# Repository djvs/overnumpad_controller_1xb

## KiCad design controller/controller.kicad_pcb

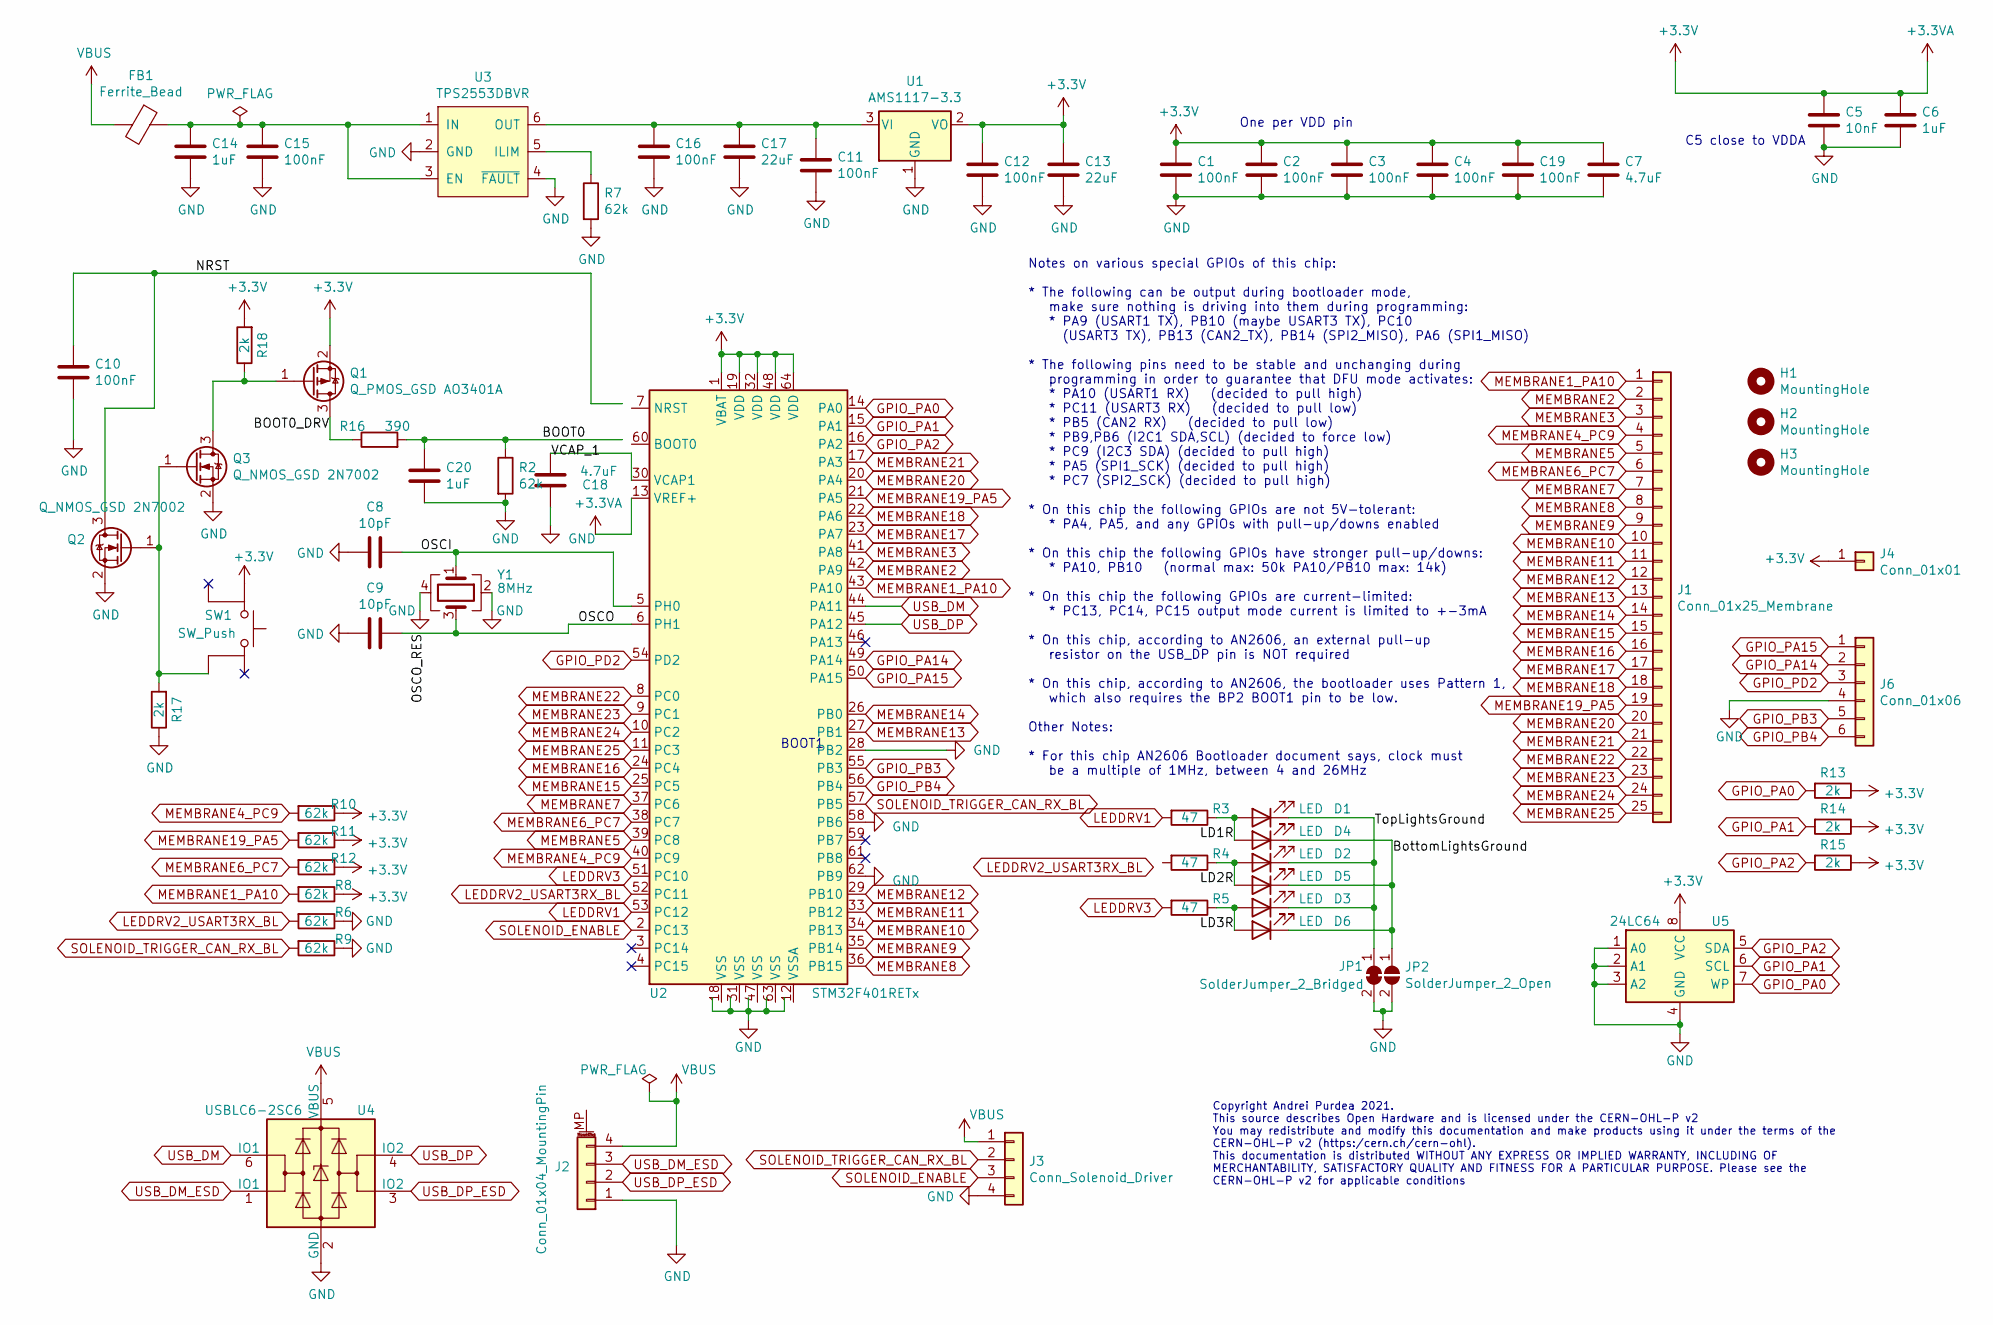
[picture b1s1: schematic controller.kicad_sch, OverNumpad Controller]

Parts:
C1, C2, C3, C4, C10, C11, C12, C15, C16, C19: 100nF; C_0805_2012Metric_Pad1.15x1.40mm_HandSolder; LCSC C49678
C5: 10nF; C_0805_2012Metric_Pad1.15x1.40mm_HandSolder; LCSC C1710
C6, C14, C20: 1uF; C_0805_2012Metric_Pad1.15x1.40mm_HandSolder; LCSC C28323
C7, C18: 4.7uF; C_0805_2012Metric_Pad1.15x1.40mm_HandSolder; LCSC C1779
C8, C9: 10pF; C_0805_2012Metric_Pad1.15x1.40mm_HandSolder; LCSC C1785
C13, C17: 22uF; C_0805_2012Metric_Pad1.15x1.40mm_HandSolder; LCSC C45783
D1, D2, D3, D4, D5, D6: LED; LED_0805_2012Metric_Pad1.15x1.40mm_HandSolder; LCSC C2296
FB1: Ferrite_Bead; L_0805_2012Metric_Pad1.15x1.40mm_HandSolder; LCSC C1015
H1, H2, H3: MountingHole; tooling_hole
J1: Conn_01x25_Membrane; membrane_connector
J2: Conn_01x04_MountingPin; JST_SH_SM04B-SRSS-TB_1x04-1MP_P1.00mm_Horizontal
J3: Conn_Solenoid_Driver; JST_PH_S4B-PH-K_1x04_P2.00mm_Horizontal
J4: Conn_01x01; PinHeader_1x01_P1.27mm_Vertical_mod_no_courtyard_no_ref
J6: Conn_01x06; PinHeader_1x06_P1.27mm_Vertical
JP1: SolderJumper_2_Bridged; shortable_shorted
JP2: SolderJumper_2_Open; shortable
Q1: Q_PMOS_GSD AO3401A; SOT-23; LCSC C700954
Q2, Q3: Q_NMOS_GSD 2N7002; SOT-23; LCSC C8545
R2, R6, R7, R8, R9, R10, R11, R12: 62k; R_0805_2012Metric_Pad1.15x1.40mm_HandSolder; LCSC C17783
R3, R4, R5: 47; R_0805_2012Metric_Pad1.15x1.40mm_HandSolder; LCSC C17714
R13, R14, R15, R17, R18: 2k; R_0805_2012Metric_Pad1.15x1.40mm_HandSolder; LCSC C17604
R16: 390; R_0805_2012Metric_Pad1.15x1.40mm_HandSolder; LCSC C17655
SW1: SW_Push; switch_K2-1187SQ-A4SW-06; LCSC C92584
U1: AMS1117-3.3; SOT-223-3_TabPin2; LCSC C6186
U2: STM32F401RETx; LQFP-64_10x10mm_P0.5mm; LCSC C69336
U3: TPS2553DBVR; SOT-23-6_Handsoldering; LCSC C55266
U4: USBLC6-2SC6; SOT-23-6; LCSC C15999
U5: 24LC64; SOIC-8_3.9x4.9mm_P1.27mm; LCSC C79988
Y1: 8MHz; Crystal_SMD_3225-4Pin_3.2x2.5mm_HandSoldering; LCSC C389817

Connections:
+3.3VA: C1.1, C2.1, C3.1, C4.1, C5.1, C6.1, C7.1, C12.1, C13.1, C19.1, J4.1, Q1.2 (S), R8.1, R10.1, R11.1, R12.1, R13.1, R14.1, R15.1, R18.2, SW1.1, U1.2 (VO), U2.1 (VBAT), U2.13 (VREF+), U2.19 (VDD), U2.32 (VDD), U2.48 (VDD), U2.64 (VDD), U5.8 (VCC)
/BOOT0: C20.1, R2.1, R16.2
/BOOT0_DRV: Q1.3 (D), R16.1
/BottomLightsGround: D4.1 (K), D5.1 (K), D6.1 (K), JP2.1 (A)
/LD1R: D1.2 (A), D4.2 (A), R3.1
/LD2R: D2.2 (A), D5.2 (A), R4.1
/LD3R: D3.2 (A), D6.2 (A), R5.1
/NRST: C10.2, Q2.3 (D)
/OSCI: C8.1, U2.5 (PH0), Y1.1
/OSCO: C9.1, U2.6 (PH1), Y1.3
/TopLightsGround: D1.1 (K), D2.1 (K), D3.1 (K), JP1.1 (A)
GND: C1.2, C2.2, C3.2, C4.2, C5.2, C6.2, C7.2, C8.2, C9.2, C10.1, C11.2, C12.2, C13.2, C14.2, C15.2, C16.2, C17.2, C18.2, C19.2, C20.2, J3.4, J6.4, JP1.2 (B), JP2.2 (B), Q2.2 (S), Q3.2 (S), R2.2, R6.1, R7.2, R9.1, R17.1, U1.1 (GND), U2.28 (PB2), U2.58 (PB6), U2.62 (PB9), U3.2 (GND), U3.4 (~FAULT), U4.2 (GND), U5.1 (A0), U5.2 (A1), U5.3 (A2), U5.4 (GND), Y1.2, Y1.4; also elsewhere on the board
GPIO_PA0: R13.2, U2.14 (PA0), U5.7 (WP)
GPIO_PA1: R14.2, U2.15 (PA1), U5.6 (SCL)
GPIO_PA2: R15.2, U2.16 (PA2), U5.5 (SDA)
GPIO_PA14: J6.2, U2.49 (PA14)
GPIO_PA15: J6.1, U2.50 (PA15)
GPIO_PB3: J6.5, U2.55 (PB3)
GPIO_PB4: J6.6, U2.56 (PB4)
GPIO_PD2: J6.3, U2.54 (PD2)
LEDDRV1: R3.2, U2.53 (PC12)
LEDDRV2_USART3RX_BL: R6.2, U2.52 (PC11)
LEDDRV3: R5.2, U2.51 (PC10)
MEMBRANE1_PA10: J1.1, R8.2, U2.43 (PA10)
MEMBRANE2: J1.2, U2.42 (PA9)
MEMBRANE3: J1.3, U2.41 (PA8)
MEMBRANE4_PC9: J1.4, R10.2, U2.40 (PC9)
MEMBRANE5: J1.5, U2.39 (PC8)
MEMBRANE6_PC7: J1.6, R12.2, U2.38 (PC7)
MEMBRANE7: J1.7, U2.37 (PC6)
MEMBRANE8: J1.8, U2.36 (PB15)
MEMBRANE9: J1.9, U2.35 (PB14)
MEMBRANE10: J1.10, U2.34 (PB13)
MEMBRANE11: J1.11, U2.33 (PB12)
MEMBRANE12: J1.12, U2.29 (PB10)
MEMBRANE13: J1.13, U2.27 (PB1)
MEMBRANE14: J1.14, U2.26 (PB0)
MEMBRANE15: J1.15, U2.25 (PC5)
MEMBRANE16: J1.16, U2.24 (PC4)
MEMBRANE17: J1.17, U2.23 (PA7)
MEMBRANE18: J1.18, U2.22 (PA6)
MEMBRANE19_PA5: J1.19, R11.2, U2.21 (PA5)
MEMBRANE20: J1.20, U2.20 (PA4)
MEMBRANE21: J1.21, U2.17 (PA3)
MEMBRANE22: J1.22, U2.8 (PC0)
MEMBRANE23: J1.23, U2.9 (PC1)
MEMBRANE24: J1.24, U2.10 (PC2)
MEMBRANE25: J1.25, U2.11 (PC3)
unnamed: Q1.1 (G), Q3.3 (D), R18.1
unnamed: Q2.1 (G), Q3.1 (G), R17.2, SW1.4
unnamed: C11.1, C16.1, C17.1, U1.3 (VI), U3.6 (OUT)
unnamed: C18.1, U2.30 (VCAP1)
unnamed: C14.1, C15.1, FB1.1, U3.1 (IN), U3.3 (EN)
unnamed: R7.1, U3.5 (ILIM)
SOLENOID_ENABLE: J3.3, U2.2 (PC13)
SOLENOID_TRIGGER_CAN_RX_BL: J3.2, R9.2, U2.57 (PB5)
USB_DM: U2.44 (PA11), U4.6 (IO1)
USB_DM_ESD: U4.1 (IO1); also elsewhere on the board
USB_DP: U2.45 (PA12), U4.4 (IO2)
USB_DP_ESD: U4.3 (IO2); also elsewhere on the board
VBUS: FB1.2, J3.1, U4.5 (VBUS); also elsewhere on the board

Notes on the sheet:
C5 close to VDDA
One per VDD pin
Notes on various special GPIOs of this chip: * The following can be output during bootloader mode, make sure nothing is driving into them during programming: * PA9 (USART1 TX), PB10 (maybe USART3 TX), PC10 (USART3 TX), PB13 (CAN2_TX), PB14 (SPI2_MISO), PA6 (SPI1_MISO) * The following pins need to b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
BOOT1
Copyright Andrei Purdea 2021. This source describes Open Hardware and is licensed under the CERN-OHL-P v2 You may redistribute and modify this documentation and make products using it under the terms of the CERN-OHL-P v2 (https:/cern.ch/cern-ohl). This documentation is distributed WITHOUT ANY EXPRE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

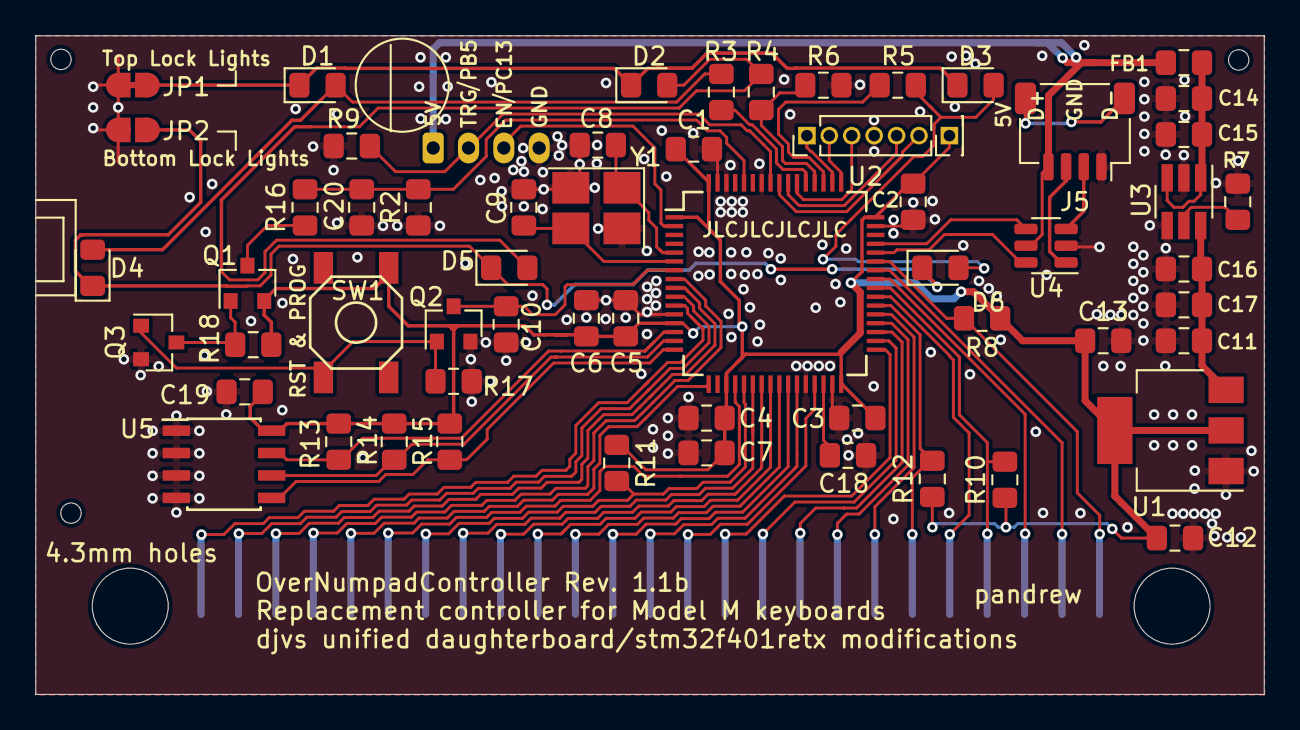
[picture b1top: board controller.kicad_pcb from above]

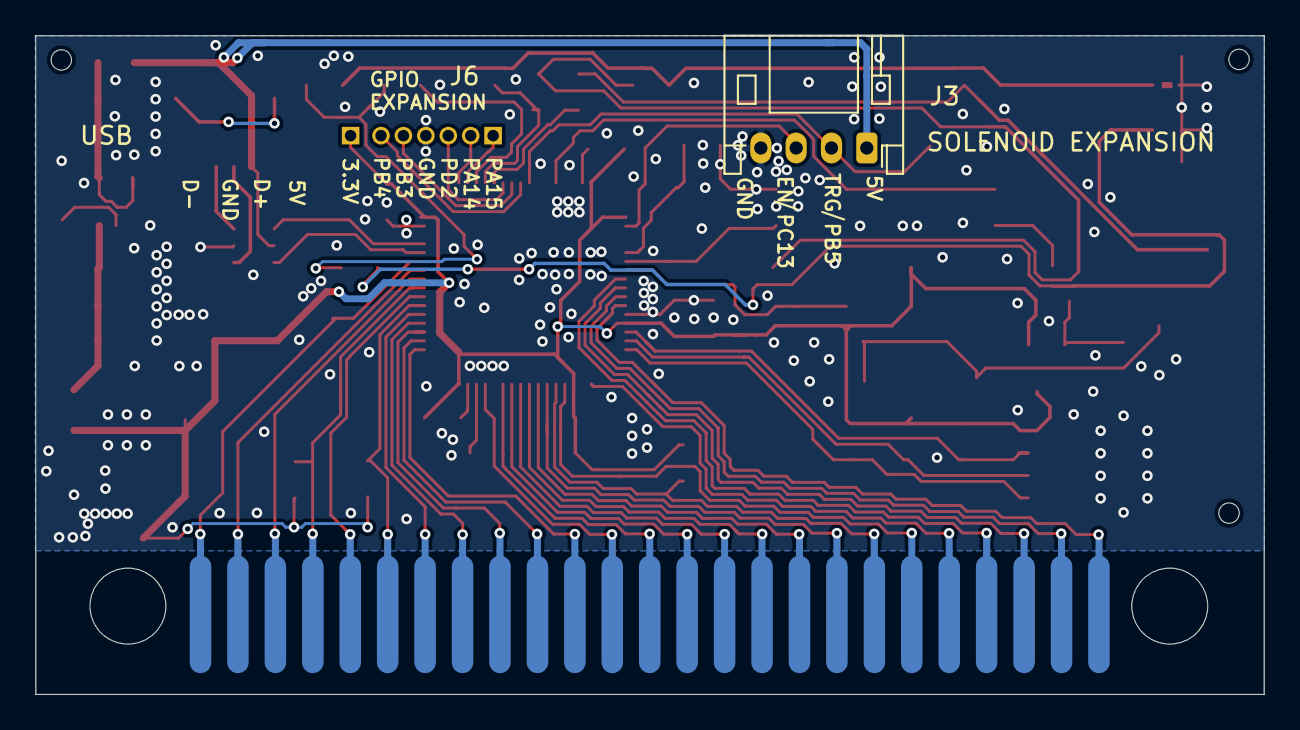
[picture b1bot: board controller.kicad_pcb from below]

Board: 2 copper layers, 69.6 x 37.3 mm, 64 parts (2 on the bottom side), 61 nets.

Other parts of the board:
J5: Conn_01x04_MountingPin; JST_SH_SM04B-SRSS-TB_1x04-1MP_P1.00mm_Horizontal

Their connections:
GND: J5.1; also elsewhere on the board
USB_DM_ESD: J5.3; also elsewhere on the board
USB_DP_ESD: J5.2; also elsewhere on the board
VBUS: J5.4; also elsewhere on the board

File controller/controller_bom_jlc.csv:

"Comment","Designator","Footprint","LCSC Part #"
"100nF","C1,C2,C3,C4,C10,C11,C12,C15,C16,C19","C_0805_2012Metric_Pad1.15x1.40mm_HandSolder","C49678"
"10nF","C5","C_0805_2012Metric_Pad1.15x1.40mm_HandSolder","C1710"
"1uF","C6,C14,C20","C_0805_2012Metric_Pad1.15x1.40mm_HandSolder","C28323"
"4.7uF","C7,C18","C_0805_2012Metric_Pad1.15x1.40mm_HandSolder","C1779"
"10pF","C8,C9","C_0805_2012Metric_Pad1.15x1.40mm_HandSolder","C296083"
"22uF","C13,C17","C_0805_2012Metric_Pad1.15x1.40mm_HandSolder","C45783"
"LED","D1,D2,D3,D4,D5,D6","LED_0805_2012Metric_Pad1.15x1.40mm_HandSolder","C2296"
"Ferrite_Bead","FB1","L_0805_2012Metric_Pad1.15x1.40mm_HandSolder","C1015"
"Q_PMOS_GSD AO3401A","Q1","SOT-23","C700954"
"Q_NMOS_GSD 2N7002","Q3,Q2","SOT-23","C8545"
"390","R1,R16","R_0805_2012Metric_Pad1.15x1.40mm_HandSolder","C17655"
"62k","R2,R7,R8,R6,R9,R11,R12,R10","R_0805_2012Metric_Pad1.15x1.40mm_HandSolder","C17783"
"47","R3,R4,R5","R_0805_2012Metric_Pad1.15x1.40mm_HandSolder","C17714"
"2k","R13,R14,R15,R18,R17","R_0805_2012Metric_Pad1.15x1.40mm_HandSolder","C17604"
"SW_Push","SW1","switch_K2-1187SQ-A4SW-06","C92584"
"AMS1117-3.3","U1","SOT-223-3_TabPin2","C6186"
"STM32F401RETx","U2","LQFP-64_10x10mm_P0.5mm","C116978"
"TPS2553DBVR","U3","SOT-23-6_Handsoldering","C55266"
"USBLC6-2SC6","U4","SOT-23-6","C7519"
"24LC64","U5","SOIC-8_3.9x4.9mm_P1.27mm","C79988"
"8MHz","Y1","Crystal_SMD_3225-4Pin_3.2x2.5mm_HandSoldering","C389817"
"Conn_01x04_MountingPin","J5","JST_SH_SM04B-SRSS-TB_1x04-1MP_P1.00mm_Horizontal","C160404"
